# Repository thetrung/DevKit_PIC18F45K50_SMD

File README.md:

DevKit PIC18F45K50-SMD / Mini-USB
===================================
Basic USB Type-B DevKit I made to learn about **PIC18F45K50** microcontroller.

- **PIC18F45K50-I/MV** will be used specifically as UQFN-40(5x5) instead DIP-40 package in previous THT version.

I actually tried to put all SMD components on front side only. Used Mini-USB instead of USB-B in previous THT version. So this isn't optimized by any mean, just simply a practice to experience what SMD PCB Design look like & what challenge compare to THT ? Although initial goal was same size to a DIP-40. But Port hints are so valuable to remove.

### 1. Basic functionality :
- USB-powered 5V supply.
- USB-HID controllable with PIC18F45k50 with D+/D- pins.
- Reset Button -> Trigger MLCR-pin pull-down -> GND.
- Programming/Debugging with PICKIT-3 via ICSP pins.
- 5 pluggable PORTS : RA, RB, RC, RD, RE.
- LED at RD0 for Blink Test.

### 2. TODO / Future extensions :
- Add Array : 
    - 4x4 12mm-Buttons pad.
    - 4x4 LEDs grid.
    - 16 Relays
      
- Add Gyro sensor.
- Add distance sensor.
- Add HLK-PM01 Module & Relay.
- Add built-in UART w/ CH340 !?
- Add LCD2004 support, with/without I2C module.
- Add WIFI/LoRA/Bluetooth by ESP32 support (?).

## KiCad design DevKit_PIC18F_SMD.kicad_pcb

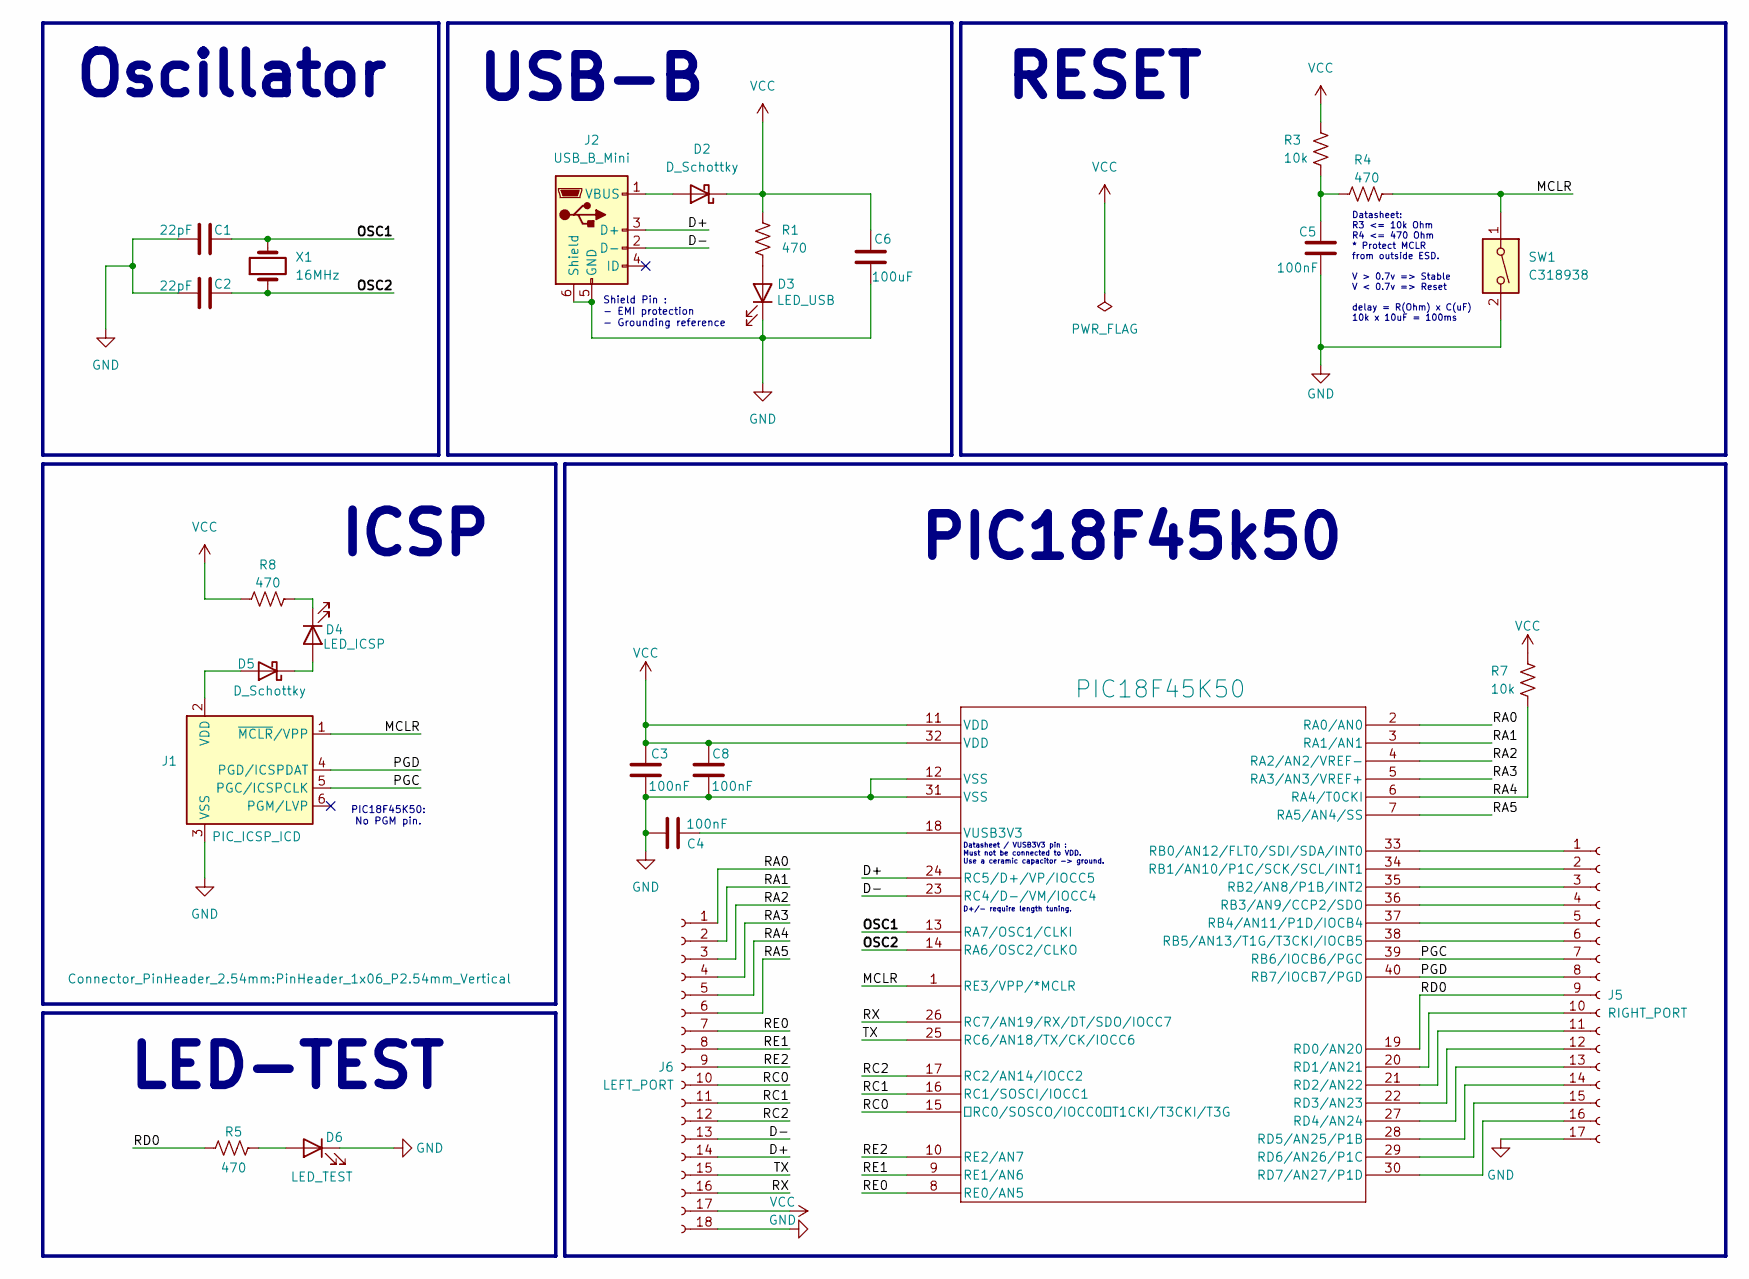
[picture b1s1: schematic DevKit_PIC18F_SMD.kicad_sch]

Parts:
C1, C2: 22pF; C_0805_2012Metric
C3, C4, C5, C8: 100nF; C_1206_3216Metric
C6: 100uF; C_1206_3216Metric
D2, D5: D_Schottky; D_0603_1608Metric
D3: LED_USB; LED_0805_2012Metric
D4: LED_ICSP; LED_0805_2012Metric
D6: LED_TEST; LED_0805_2012Metric
J1: PIC_ICSP_ICD; PinHeader_1x06_P2.54mm_Vertical
J2: USB_B_Mini; USB_Mini-B_Tensility_54-00023_Vertical
J5: RIGHT_PORT; PinHeader_1x17_P2.54mm_Vertical
J6: LEFT_PORT; PinHeader_1x18_P2.54mm_Vertical
PIC18F45K50: PIC18F45K50-I/MV; QFN-40-1EP_5x5mm_P0.4mm_EP3.6x3.6mm
R1, R4, R5, R8: 470; R_0805_2012Metric
R3, R7: 10k; R_1206_3216Metric
SW1: C318938; SW_SPST_SKQG_WithStem
X1: 16MHz; Crystal_SMD_2520-4Pin_2.5x2.0mm

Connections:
/D+: J2.3 (D+), J6.14, PIC18F45K50.24 (RC5/D+/VP/IOCC5)
/D-: J2.2 (D-), J6.13, PIC18F45K50.23 (RC4/D-/VM/IOCC4)
/MCLR: J1.1 (~MCLR/VPP), PIC18F45K50.1 (RE3/VPP/*MCLR), R4.1, SW1.1
/OSC1: C1.1, PIC18F45K50.13 (RA7/OSC1/CLKI), X1.2
/OSC2: C2.1, PIC18F45K50.14 (RA6/OSC2/CLKO), X1.1
/PGC: J1.5 (PGC/ICSPCLK), J5.7, PIC18F45K50.39 (RB6/IOCB6/PGC)
/PGD: J1.4 (PGD/ICSPDAT), J5.8, PIC18F45K50.40 (RB7/IOCB7/PGD)
/RA0: J6.1, PIC18F45K50.2 (RA0/AN0)
/RA1: J6.2, PIC18F45K50.3 (RA1/AN1)
/RA2: J6.3, PIC18F45K50.4 (RA2/AN2/VREF-)
/RA3: J6.4, PIC18F45K50.5 (RA3/AN3/VREF+)
/RA4: J6.5, PIC18F45K50.6 (RA4/T0CKI), R7.2
/RA5: J6.6, PIC18F45K50.7 (RA5/AN4/SS)
/RC0: J6.10, PIC18F45K50.15 (RC0/SOSCO/IOCC0 T1CKI/T3CKI/T3G)
/RC1: J6.11, PIC18F45K50.16 (RC1/SOSCI/IOCC1)
/RC2: J6.12, PIC18F45K50.17 (RC2/AN14/IOCC2)
/RD0: J5.9, PIC18F45K50.19 (RD0/AN20), R5.1
/RE0: J6.7, PIC18F45K50.8 (RE0/AN5)
/RE1: J6.8, PIC18F45K50.9 (RE1/AN6)
/RE2: J6.9, PIC18F45K50.10 (RE2/AN7)
/RX: J6.16, PIC18F45K50.26 (RC7/AN19/RX/DT/SDO/IOCC7)
/TX: J6.15, PIC18F45K50.25 (RC6/AN18/TX/CK/IOCC6)
GND: C1.2, C2.2, C3.2, C4.1, C5.1, C6.1, C8.2, D3.1 (K), D6.1 (K), J1.3 (VSS), J2.5 (GND), J2.6 (Shield), J5.17, J6.18, PIC18F45K50.12 (VSS), PIC18F45K50.31 (VSS), SW1.2
unnamed: C5.2, R3.2, R4.2
unnamed: D2.2 (A), J2.1 (VBUS)
unnamed: D3.2 (A), R1.2
unnamed: D4.2 (A), D5.1 (K)
unnamed: D4.1 (K), R8.2
unnamed: D5.2 (A), J1.2 (VDD)
unnamed: D6.2 (A), R5.2
unnamed: J5.1, PIC18F45K50.33 (RB0/AN12/FLT0/SDI/SDA/INT0)
unnamed: J5.2, PIC18F45K50.34 (RB1/AN10/P1C/SCK/SCL/INT1)
unnamed: J5.3, PIC18F45K50.35 (RB2/AN8/P1B/INT2)
unnamed: J5.4, PIC18F45K50.36 (RB3/AN9/CCP2/SDO)
unnamed: J5.5, PIC18F45K50.37 (RB4/AN11/P1D/IOCB4)
unnamed: J5.6, PIC18F45K50.38 (RB5/AN13/T1G/T3CKI/IOCB5)
unnamed: J5.10, PIC18F45K50.20 (RD1/AN21)
unnamed: J5.11, PIC18F45K50.21 (RD2/AN22)
unnamed: J5.12, PIC18F45K50.22 (RD3/AN23)
unnamed: J5.13, PIC18F45K50.27 (RD4/AN24)
unnamed: J5.14, PIC18F45K50.28 (RD5/AN25/P1B)
unnamed: J5.15, PIC18F45K50.29 (RD6/AN26/P1C)
unnamed: J5.16, PIC18F45K50.30 (RD7/AN27/P1D)
unnamed: C4.2, PIC18F45K50.18 (VUSB3V3)
VCC: C3.1, C6.2, C8.1, D2.1 (K), J6.17, PIC18F45K50.11 (VDD), PIC18F45K50.32 (VDD), R1.1, R3.1, R7.1, R8.1

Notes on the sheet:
RESET
USB-B
D+/- require length tuning.
ICSP
Shield Pin : - EMI protection - Grounding reference
Datasheet / VUSB3V3 pin : Must not be connected to VDD. Use a ceramic capacitor -> ground.
LED-TEST
Datasheet: R3 <= 10k Ohm R4 <= 470 Ohm * Protect MCLR from outside ESD. V > 0.7v => Stable V < 0.7v => Reset delay = R(Ohm) x C(uF) 10k x 10uF = 100ms
Oscillator
PIC18F45K50: No PGM pin.
PIC18F45k50

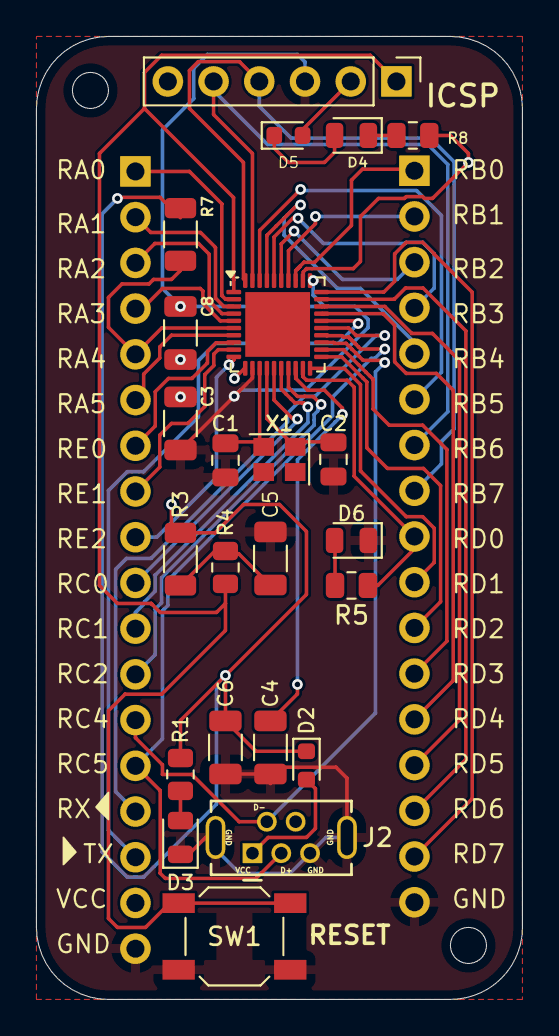
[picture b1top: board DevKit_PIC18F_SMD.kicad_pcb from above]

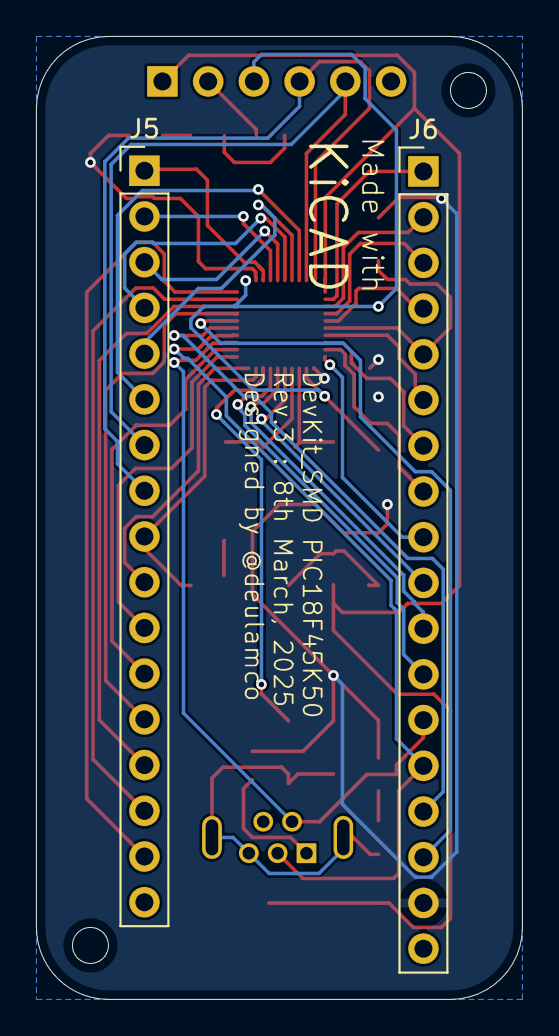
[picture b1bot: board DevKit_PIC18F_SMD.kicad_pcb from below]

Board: 2 copper layers, 27.0 x 53.5 mm, 25 parts (2 on the bottom side), 45 nets.

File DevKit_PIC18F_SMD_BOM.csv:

"Id";"Designator";"Footprint";"Quantity";"Designation";"Supplier and ref";
1;"J2";"USB_Mini-B_Tensility_54-00023_Vertical";1;"USB_B_Mini";;;
2;"SW1";"SW_Tactile_SPST_NO_Straight_CK_PTS636Sx25SMTRLFS";1;"C318938";;;
3;"R8,R4,R1";"R_0805_2012Metric";3;"470";;;
4;"D6";"LED_0805_2012Metric";1;"LED_TEST";;;
5;"D4";"LED_0805_2012Metric";1;"LED_ICSP";;;
6;"D3";"LED_0805_2012Metric";1;"LED_USB";;;
7;"C2,C1";"C_0805_2012Metric";2;"22pF";;;
8;"J1";"PinHeader_1x06_P2.54mm_Vertical";1;"PIC_ICSP_ICD";;;
9;"C3,C5,C4,C8";"C_1206_3216Metric";4;"100nF";;;
10;"PIC18F45K50";"QFN-40-1EP_5x5mm_P0.4mm_EP3.6x3.6mm";1;"PIC18F45K50-I/MV";;;
11;"X1";"Crystal_SMD_2520-4Pin_2.5x2.0mm";1;"16MHz";;;
12;"D2,D5";"D_0603_1608Metric";2;"D_Schottky";;;
13;"R3,R7";"R_1206_3216Metric";2;"10k";;;
14;"C6";"C_1206_3216Metric";1;"100uF";;;
15;"R5";"R_1206_3216Metric";1;"470";;;
16;"J5";"PinHeader_1x17_P2.54mm_Vertical";1;"RIGHT_PORT";;;
17;"J6";"PinHeader_1x18_P2.54mm_Vertical";1;"LEFT_PORT";;;

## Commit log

2025-03-04 made SMD version of prev DevKit rev.5
2025-03-04 update images & comment.
2025-03-05 Added VCC/GND pins
2025-03-05 Remove PWR flag in Reset part, since we updated wrong pin setup in symbol PIC18F45K50.
2025-03-07 rev.2 : and GND -> Left sockets & move RST_Button to bottom.
2025-03-07 Add mapped BOM+CPL
2025-03-07 Optimize BOM cost to ~0/2pcs but minium 6 in total.
2025-03-08 Rev.3 : refine part-selection for JLCPCB fabrication & silkscreen.
2025-03-08 Fix R5 size 1206 -> 0805 & BOM of D5,D2 -> C3758192
2025-03-10 :Fix R5 size 1206 -> 0805 & BOM of D5,D2 -> C3758192
